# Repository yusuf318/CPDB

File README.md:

# CPDB
Yeniay Control Power Distribution Board

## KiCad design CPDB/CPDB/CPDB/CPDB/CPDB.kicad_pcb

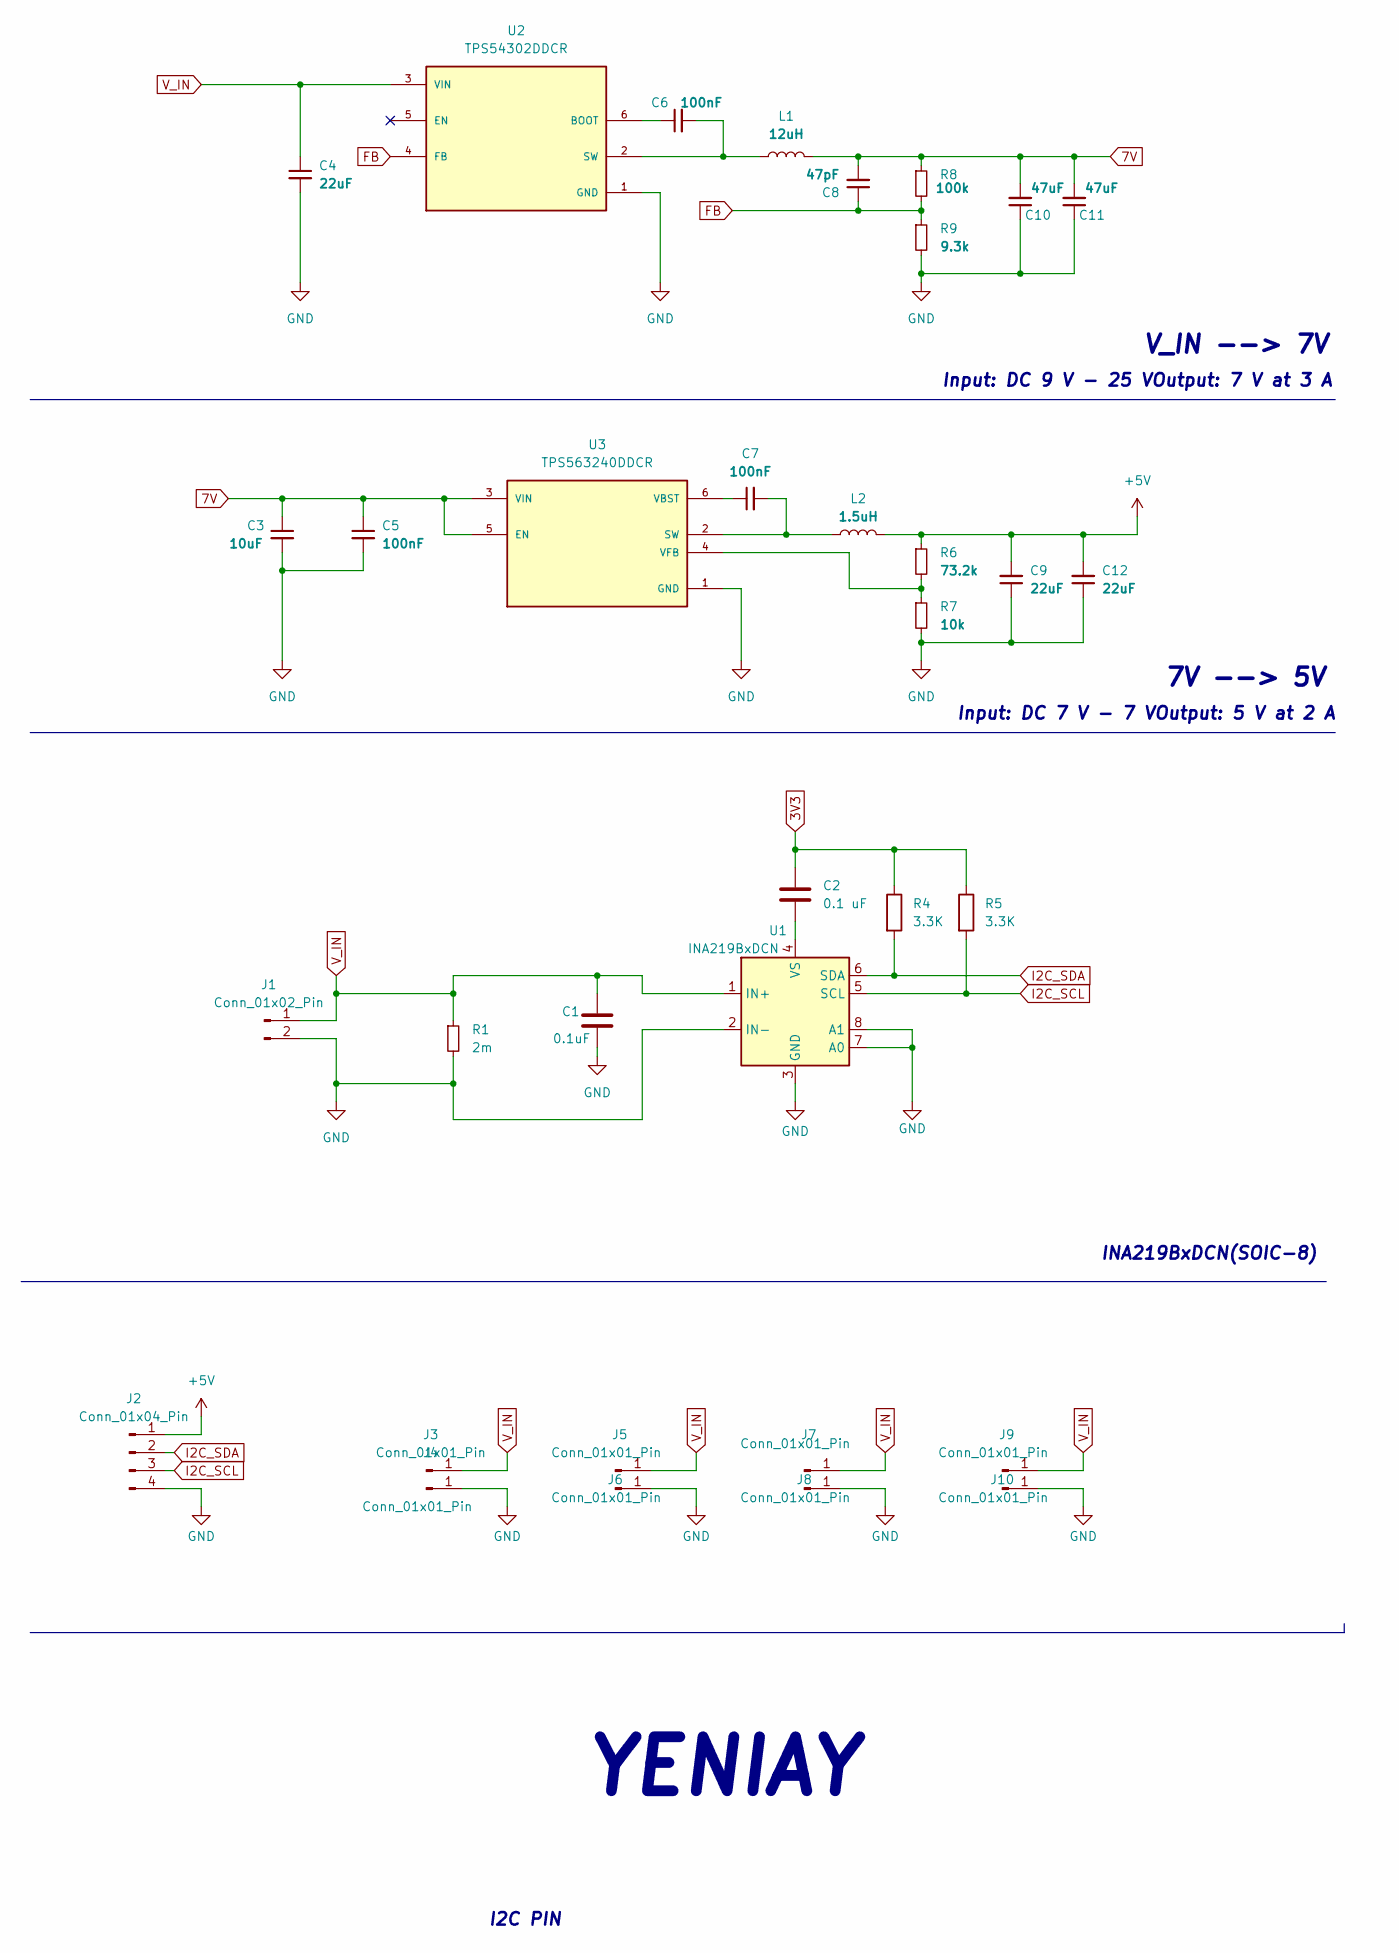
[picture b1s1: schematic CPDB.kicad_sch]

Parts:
C1: 0.1uF; C_0603_1608Metric
C2: 0.1 uF; C_0603_1608Metric
C3: 10uF; C_0805_2012Metric
C4, C9, C12: 22uF; C_0805_2012Metric
C5, C6, C7: 100nF; C_0603_1608Metric
C8: 47pF; C_0603_1608Metric
C10, C11: 47uF; C_0805_2012Metric
J1: Conn_01x02_Pin; PinHeader_1x02_P1.00mm_Vertical_SMD_Pin1Left
J2: Conn_01x04_Pin; PinHeader_1x04_P1.00mm_Vertical_SMD_Pin1Left
J3, J4, J5, J6, J7, J8, J9, J10: Conn_01x01_Pin; Samtec_HPM-01-05-x-S_Straight_1x01_Pitch5.08mm
L1: 12uH; L_Sunlord_SWPA6045S
L2: 1.5uH; L_Coilcraft_XAL4020-XXX
R1: 2m; R_2512_6332Metric
R4, R5: 3.3K; R_0805_2012Metric
R6: 73.2k; R_0805_2012Metric
R7: 10k; R_0805_2012Metric
R8: 100k; R_0805_2012Metric
R9: 9.3k; R_0805_2012Metric
U1: INA219BxDCN; SOT-23-8
U2: TPS54302DDCR; SOT95P280X110-6N; PARTREV A
U3: TPS563240DDCR; SOT95P280X110-6N; PARTREV A

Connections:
3V3: C2.1, R4.1, R5.1
7V: C3.1, C5.1, C8.2, C10.2, C11.2, L1.2, R8.1, U3.3 (VIN), U3.5 (EN)
+5V: C9.2, C12.2, J2.1, L2.2, R6.1
FB: C8.1, R8.2, R9.1, U2.4 (FB)
GND: C1.2, C3.2, C4.2, C5.2, C9.1, C10.1, C11.1, C12.1, J1.2, J2.4, J4.1, J6.1, J8.1, J10.1, R1.2, R7.2, R9.2, U1.2 (IN-), U1.3 (GND), U1.7 (A0), U1.8 (A1), U2.1 (GND), U3.1 (GND)
I2C_SCL: J2.3, R5.2, U1.5 (SCL)
I2C_SDA: J2.2, R4.2, U1.6 (SDA)
unnamed: C2.2, U1.4 (VS)
unnamed: C6.1, U2.6 (BOOT)
unnamed: C6.2, L1.1, U2.2 (SW)
unnamed: C7.2, L2.1, U3.2 (SW)
unnamed: C7.1, U3.6 (VBST)
unnamed: R6.2, R7.1, U3.4 (VFB)
V_IN: C1.1, C4.1, J1.1, J3.1, J5.1, J7.1, J9.1, R1.1, U1.1 (IN+), U2.3 (VIN)

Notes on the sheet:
INA219BxDCN(SOIC-8)
YENIAY
Input: DC 7 V - 7 VOutput: 5 V at 2 A
I2C PIN
Input: DC 9 V - 25 VOutput: 7 V at 3 A
V_IN --> 7V
7V --> 5V

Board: 2 copper layers, 34 parts (0 on the bottom side), 14 nets, no tracks yet.

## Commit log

2025-02-13 name correcting
2025-02-15 Edge cuts dxf file added. | CPDB.docx created.
2025-02-16 Modules folder added.
2025-02-19 test
2025-02-20 INA219 sematigi eklendi.
2025-02-20 Voltage regulator done
2025-02-21 Voltage Regulator warnings are resolved
2025-02-21 Word file updated
2025-02-21 ina219
2025-02-21 INA219 and Regulators added.
2025-02-23 CPDB schematic updated
2025-07-12 Schematic completed.
2025-07-12 gruplama yapıldı, indüktörler değişti
2025-07-13 ESC pin placement.
